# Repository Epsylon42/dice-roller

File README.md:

# Dice-Roller

Electronic dice roller for all the dice rolling needs. Includes d4, d6, d8, d10, d12 and d20.

Partially implemented:
* Battery display (currently shows raw analog pin input, without converting it to voltage or %)
* d100 / percentile dice (can be done by holding down d10 button, but is has not been finished and currently does not work correctly)

This repository contains two PCB versions - v1 and v2.
* v1 has been built and tested, but the kicad files have been lost. The recovered gerbers are in `dice-roller-pcb/v1-gerbers`.
* v2 is in the actual kicad project. It is meant to support battery charging status and persistent settings, but most of it is not implemented.

The firmware supports either version, selected via platformio environments

## Building firmware

* Install platformio
* Download dependencies: `git submodule update --init`
* Apply `firmware/lib/Adafruit-GFX-Library.patch` to `firmware/lib/Adafruit-GFX-Library`
  * The OLED display is installed upside-down on the PCB, and this patch includes a horrible hack to flip the text.
* Build firmware using platformio: `pio run -e v1` or `pio run -e v2`, depending on the target pcb version

Firmware is flashed via the UART header. To enable esp8266 flashing mode - hold the 0 button when booting

## Pictures

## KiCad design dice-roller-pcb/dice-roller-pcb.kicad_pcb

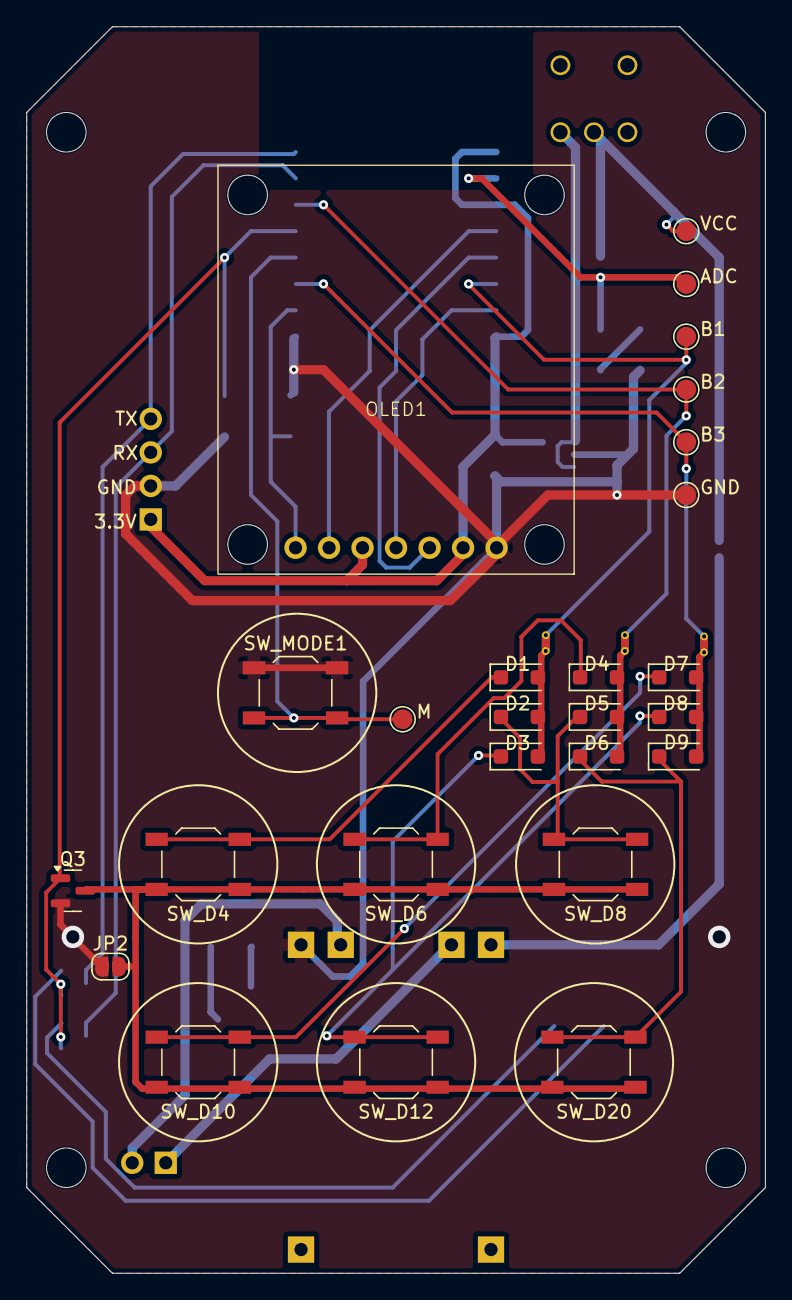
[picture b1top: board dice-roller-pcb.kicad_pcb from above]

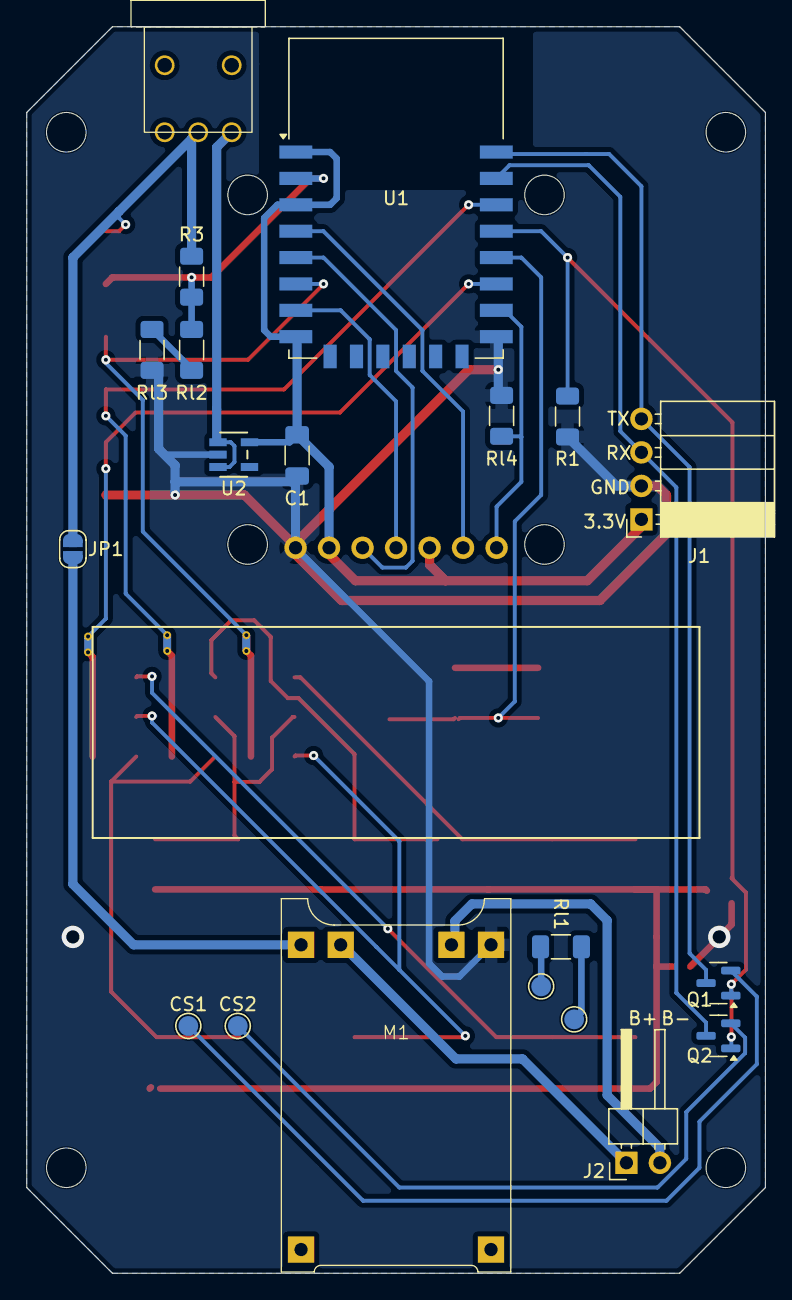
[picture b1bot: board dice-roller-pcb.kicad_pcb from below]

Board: 2 copper layers, 56.0 x 94.5 mm, 47 parts (18 on the bottom side), 32 nets.

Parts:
C1: 10uF; C_1206_3216Metric_Pad1.33x1.80mm_HandSolder
CS1, CS2: TestPoint; TestPoint_Pad_D1.5mm
D1, D2, D3, D4, D5, D6, D7, D8, D9: 1N4148W; D_SOD-123F
J1: Conn_01x04_Pin; PinSocket_1x04_P2.54mm_Horizontal
J2: Conn_01x02_Socket; PinHeader_1x02_P2.54mm_Horizontal
JP1, JP2: SolderJumper_2_Open; SolderJumper-2_P1.3mm_Open_RoundedPad1.0x1.5mm
M1: TP4056-USBC
NT14, NT15, NT16: NetTie_2; NetTie-2_THT_Pad0.3mm
OLED1: OLED
Q1, Q2, Q3: AO3400; SOT-23
R1, R3: 100K; R_1206_3216Metric_Pad1.30x1.75mm_HandSolder
Rl1, Rl2, Rl3, Rl4: 10K; R_1206_3216Metric_Pad1.30x1.75mm_HandSolder
SW_D4, SW_D6, SW_D8, SW_D10, SW_D12, SW_D20: SW_Push; SW_SPST_TL3342
SW_MODE1: SW_Push; SW_SPST_TL3342
SW_POWER1: SW_DPDT_x2; SW
TP1, TP2, TP3, TP4, TP5, TP6, TP8: TestPoint; TestPoint_Pad_D1.5mm
U1: ESP-12F; ESP-12E
U2: RT9013-33GB; SOT-23-5_RIT

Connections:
+3.3V: C1.2, J1.1, OLED1.2 (VCC), OLED1.5 (RES), U1.1 (~RST), U1.3 (EN), U1.8 (VCC), U2.5 (VOUT)
/ADC: R3.2, Rl2.2, TP5.1 (1_1), U1.2 (ADC)
/B1: NT14.1, TP3.1 (1_1), U1.6 (GPIO12)
/B1_BUS: D1.2 (A), D2.2 (A), D3.2 (A), NT14.2
/B2: NT15.1, TP2.1 (1_1), U1.20 (GPIO5)
/B2_BUS: D4.2 (A), D5.2 (A), D6.2 (A), NT15.2
/B3: NT16.1, TP1.1 (1_1), U1.17 (GPIO2)
/B3_BUS: D7.2 (A), D8.2 (A), D9.2 (A), NT16.2
/B+: J2.1, M1.3 (B+)
/B-: J2.2, M1.4 (B-)
/CHIP_RX: J1.3, Q2.3 (D), U1.21 (GPIO3/RXD)
/CHIP_TX: J1.4, Q1.3 (D), U1.22 (GPIO1/TXD)
/COPI: OLED1.4 (SDA), U1.7 (GPIO13)
/CS: OLED1.7 (SC), Rl4.2, U1.16 (GPIO15)
/CS1: CS1.1 (1_1), Q1.2 (S)
/CS2: CS2.1 (1_1), Q2.2 (S)
/MODE_SW: SW_MODE1.2, TP8.1 (1_1), U1.18 (GPIO0)
/OLED_DC: OLED1.6 (DC), U1.4 (GPIO16)
/PERIPHERAL_EN: Q1.1 (G), Q2.1 (G), Q3.1 (G), R1.1, U1.19 (GPIO4)
/SCLK: OLED1.3 (SCL), U1.5 (GPIO14)
GND: C1.1, J1.2, JP2.1 (A), M1.6 (OUT-), OLED1.1 (GND), Q3.2 (S), R1.2, Rl3.1, Rl4.1, SW_MODE1.1, TP4.1 (1_1), U1.15 (GND), U2.2 (GND)
unnamed: D1.1 (K), SW_D4.2
unnamed: D2.1 (K), D5.1 (K), SW_D8.2
unnamed: D3.1 (K), D8.1 (K), SW_D12.2
unnamed: D4.1 (K), SW_D6.2
unnamed: D6.1 (K), D9.1 (K), SW_D20.2
unnamed: D7.1 (K), SW_D10.2
unnamed: JP1.1 (A), M1.5 (OUT+)
unnamed: JP2.2 (B), Q3.3 (D), SW_D4.1, SW_D6.1, SW_D8.1, SW_D10.1, SW_D12.1, SW_D20.1
unnamed: Rl2.1, Rl3.2
unnamed: SW_POWER1.3 (C), U2.1 (VIN), U2.3 (EN)
VCC: JP1.2 (B), R3.1, SW_POWER1.2 (B), TP6.1 (1_1)

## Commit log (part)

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2024-11-02 Import project
2024-11-02 Add README
